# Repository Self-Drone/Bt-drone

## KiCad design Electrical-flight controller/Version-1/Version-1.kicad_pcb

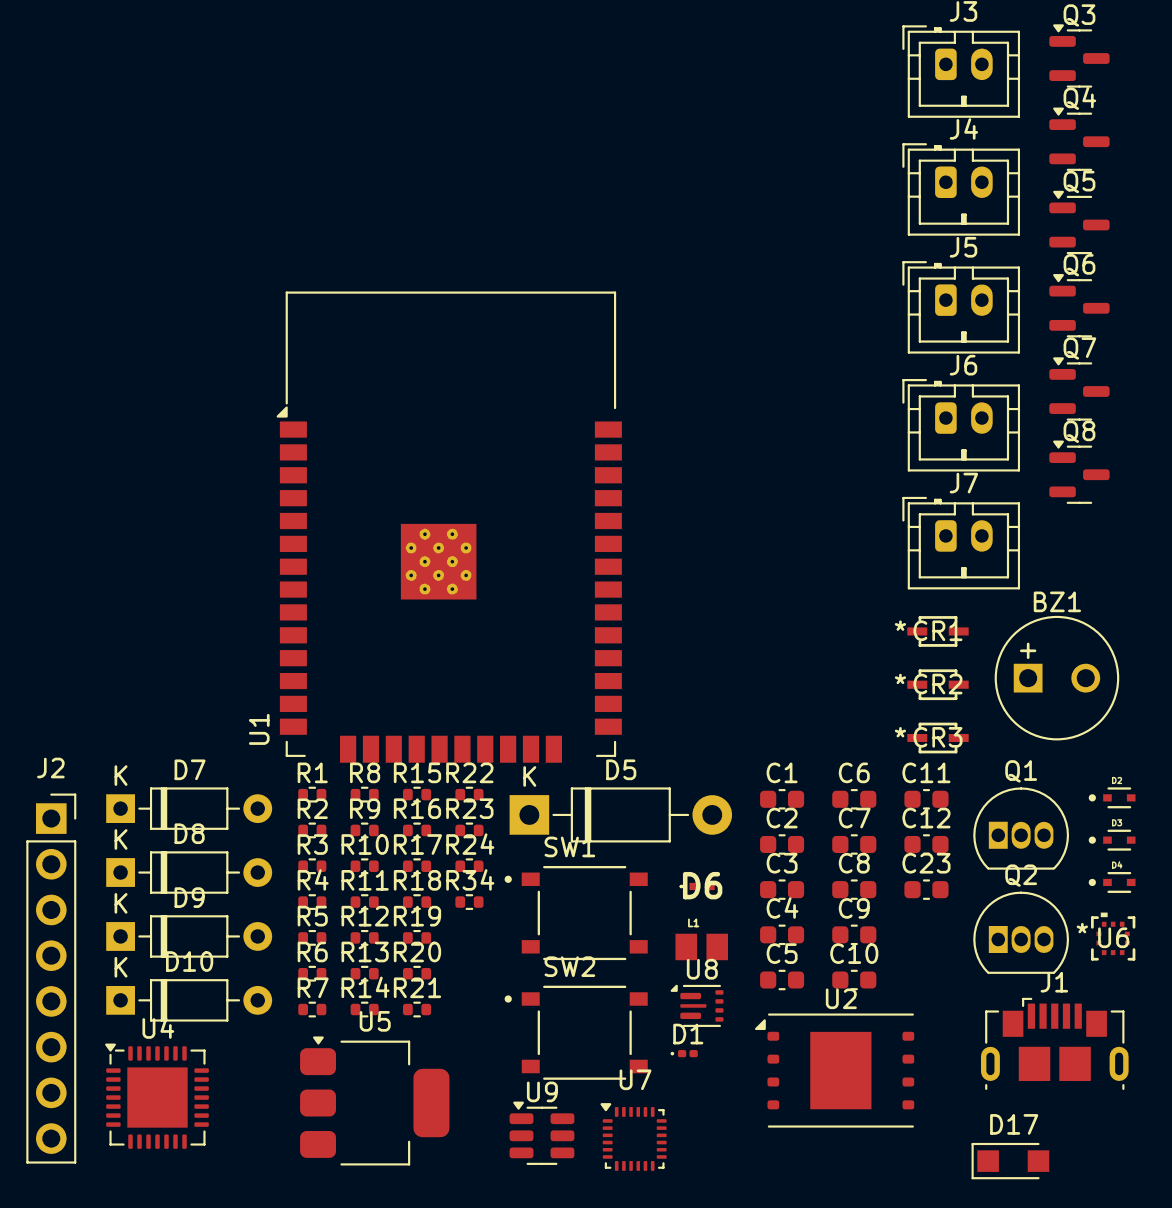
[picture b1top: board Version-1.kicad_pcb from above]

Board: 4 copper layers, 79 parts (0 on the bottom side), 52 nets, no tracks yet.

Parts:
BZ1: Buzzer; MagneticBuzzer_Kingstate_KCG0601
C1, C3, C4, C9, C23: 10uF; C_0603_1608Metric
C2, C5, C6: 0.1uF; C_0603_1608Metric
C7, C8: 1nF; C_0603_1608Metric
C10, C11, C12: 22uF; C_0603_1608Metric
CR1, CR2, CR3: 1SS404_H3FT; USC_TOS
D1: LED; LED_0201_0603Metric
D2, D3, D4: LESD5D5.0CT1G; TVS_LESD5D5.0CT1G
D5: 1N5819; D_DO-41_SOD81_P10.16mm_Horizontal
D6: ESD3.3V88D-C; ESD33v88DC
D7, D8, D9, D10: 1N4148; D_DO-35_SOD27_P7.62mm_Horizontal
D17: PMEG6020ER; Nexperia_CFP3_SOD-123W
J1: USB_B_Micro; USB_Micro-B_GCT_USB3076-30-A
J2: Conn_01x08_Socket; PinSocket_1x08_P2.54mm_Vertical
J3, J4, J5, J6, J7: Conn_01x02_Socket; JST_PH_B2B-PH-K_1x02_P2.00mm_Vertical
L1: 1uH; INDC2012X105N
Q1, Q2: S8050; TO-92_Inline
Q3, Q5, Q6, Q7: AO3400A; SOT-23
Q4: BSS138; SOT-23
Q8: DMG2301L; SOT-23
R1, R2, R3, R5, R6, R7: 0; R_0402_1005Metric
R4: 2K; R_0402_1005Metric
R8, R9, R10, R11, R12, R13, R14: 10K; R_0402_1005Metric
R15, R16: 47R; R_0402_1005Metric
R17: 732K; R_0402_1005Metric
R18: 100K; R_0402_1005Metric
R19, R20, R21, R22, R23, R24: 4k7; R_0402_1005Metric
R34: 2k2; R_0402_1005Metric
SW1, SW2: SW_MEC_5G; SW_TS-1187A-B-A-B
U1: ESP32-WROOM-32
U2: W25Q128JVE; WSON-8-1EP_8x6mm_P1.27mm_EP3.4x4.3mm
U4: CP2102N-Axx-xQFN28; QFN-28-1EP_5x5mm_P0.5mm_EP3.35x3.35mm
U5: AMS1117; SOT-223-3_TabPin2
U6: BMP390L
U7: ICM-20948; InvenSense_QFN-24_3x3mm_P0.4mm
U8: TPS61022; Texas_RWU0007A_VQFN-7_2x2mm_P0.5mm
U9: LTC4412xS6; TSOT-23-6

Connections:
3.3v: BZ1.1 (+), C4.1, C5.1, CR1.2, CR2.2, D6.1 (A1), J2.3, R14.1, R19.1, R20.1, R21.1, R22.1, R23.1, R24.1, U1.2 (VDD), U2.8 (VCC), U4.6 (VDD), U4.7 (VREGIN), U5.2 (VO), U6.1 (VDDIO), U6.6 (CSB), U6.10 (VDD), U7.8 (VDDIO), U7.13 (VDD), U7.22 (~CS)
5v: C1.1, C2.1, D5.1 (K), D17.2 (A), U4.8 (VBUS)
BAT+: C9.1, J3.1, L1.1, U8.5 (EN), U8.7 (VIN)
BAT_IN: C10.1, C11.1, C12.1, D7.1 (K), D8.1 (K), D9.1 (K), D10.1 (K), J4.2, J5.2, J6.2, J7.2, Q8.3 (D), R17.1, U8.3 (VOUT), U9.1 (VIN)
BUZZER: Q4.1 (G), R34.1, U1.33 (IO21)
CS: U1.9 (IO33), U2.1 (~CS)
CTS: R7.2, U4.23 (~CTS)
DI: U1.27 (IO16), U2.5 (DI/IO_{0})
DO: U1.28 (IO17), U2.2 (DO/IO_{1})
DTR: Q2.1 (E), R8.1, U4.28 (~DTR)
EN: C6.1, Q1.3 (C), R14.2, R16.1, U1.3 (EN)
GND: C1.2, C2.2, C3.2, C4.2, C5.2, C6.2, C7.1, C8.1, C9.2, C10.2, C11.2, C12.2, C23.2, D1.1 (K), D2.2 (A2), D3.2 (A2), D4.2 (A2), D6.2 (A2), J1.5 (GND), J2.4, J2.8, J3.2, Q3.2 (S), Q4.2 (S), Q5.2 (S), Q6.2 (S), Q7.2 (S), R10.2, R11.2, R12.2, R13.2, R18.2, R34.2, U1.1 (GND), U1.15 (GND), U1.38 (GND), U1.39 (GND), U2.4 (GND), U2.9 (EP), U4.3 (GND), U4.29 (GND), U5.1 (ADJ), U6.3 (VSS), U6.8 (VSS), U6.9 (VSS), U7.18 (GND), U7.20 (GND), U8.1 (GND), U9.2 (GND), U9.3 (CTL)
I2C-CL: J2.1, R20.2, R21.2, R24.2, U1.36 (IO22), U6.2 (SCK), U7.23 (SCL/SCLK)
I2C-D: J2.2, R19.2, R22.2, R23.2, U1.7 (IO35), U6.4 (SDI), U7.24 (SDA/SDI)
IO0: Q2.3 (C), R15.1, U1.25 (IO0)
IO13: R6.1, U1.16 (IO13)
IO15: R7.1, U1.23 (IO15)
MISO: J2.6, U1.31 (IO19)
MOSI: J2.7, U1.37 (IO23)
unnamed: BZ1.2 (-), Q4.3 (D)
unnamed: C7.2, R15.2
unnamed: C8.2, R16.2
unnamed: D1.2 (A), R4.2
unnamed: D3.1 (A1), J1.3 (D+), R1.1
unnamed: D4.1 (A1), J1.2 (D-), R2.1
unnamed: D7.2 (A), J4.1, Q3.3 (D)
unnamed: D8.2 (A), J5.1, Q5.3 (D)
unnamed: D9.2 (A), J6.1, Q6.3 (D)
unnamed: D10.2 (A), J7.1, Q7.3 (D)
unnamed: Q1.2 (B), R8.2
unnamed: Q2.2 (B), R9.2
unnamed: Q8.1 (G), U9.5 (GATE)
unnamed: CR3.1, U5.3 (VI)
unnamed: CR2.1, U6.5 (SDO)
unnamed: CR1.1, U7.9 (SDO/AD0)
unnamed: R17.2, R18.1, U8.4 (FB)
unnamed: L1.2, U8.2 (SW)
RTS: Q1.1 (E), R6.2, R9.1, U4.24 (~RTS)
RXD: R5.2, U4.25 (RXD)
RXD0: R5.1, U1.34 (RXD0/IO3)
SCK: J2.5, U1.30 (IO18)
SCK_flash: U1.13 (IO14), U2.6 (CLK)
SWITCHOUT: C3.1, C23.1, CR3.2, D17.1 (K), Q8.2 (S), R4.1, U9.6 (SENSE)
TXD: R3.2, U4.26 (TXD)
TXD0: R3.1, U1.35 (TXD0/IO1)
USB_DN: R2.2, U4.5 (D-)
USB_DP: R1.2, U4.4 (D+)
esc_1: Q3.1 (G), R10.1, U1.10 (IO25)
esc_2: Q7.1 (G), R13.1, U1.11 (IO26)
esc_3: Q5.1 (G), R11.1, U1.12 (IO27)
esc_4: Q6.1 (G), R12.1, U1.8 (IO32)
power_in: D2.1 (A1), D5.2 (A), J1.1 (VBUS)

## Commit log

2025-03-04 schematic upload
2025-03-05 updated schematic
2025-04-21 Started ESP32
2025-04-24 2nd update
2025-04-25 power circuit
2025-04-25 Pwoer supply
2025-04-26 flash chip, reset switches , mc etc
2025-05-01 esp32-s3 power module
2025-05-03 esp32-swich over downloaded footpirnt and .sym files
2025-05-21 light earlier changes
2025-05-21 some changes in wiring of IMU and flash and bmp -> not fully done:(
2025-05-29 main schemtic done!!
2025-06-11 escs
2025-06-12 added motor drivers
2025-06-13 schematic complete!
2025-06-17 imported footprints and assigned them
2025-06-22 started pcb -- all basic setups
2025-08-13 bt drone_1
